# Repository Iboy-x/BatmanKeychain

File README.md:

# Batman Keychain

Wanted to save Gotham and proove your friends that you are Batman ? This Keychain is best!

## Schematic

## PCB

## 3D view

## Features
- LED on eyes that works when you press the button
- Motor that vibrates in pressing button 

## BOM
- 1 	Battery holder
- 2   LEDs 
- 2 	220 Resistor
- 1 	Push Button
- 1   Motor DC vibrator

Made by `@AbdulMoiz Adeel` on slack :D

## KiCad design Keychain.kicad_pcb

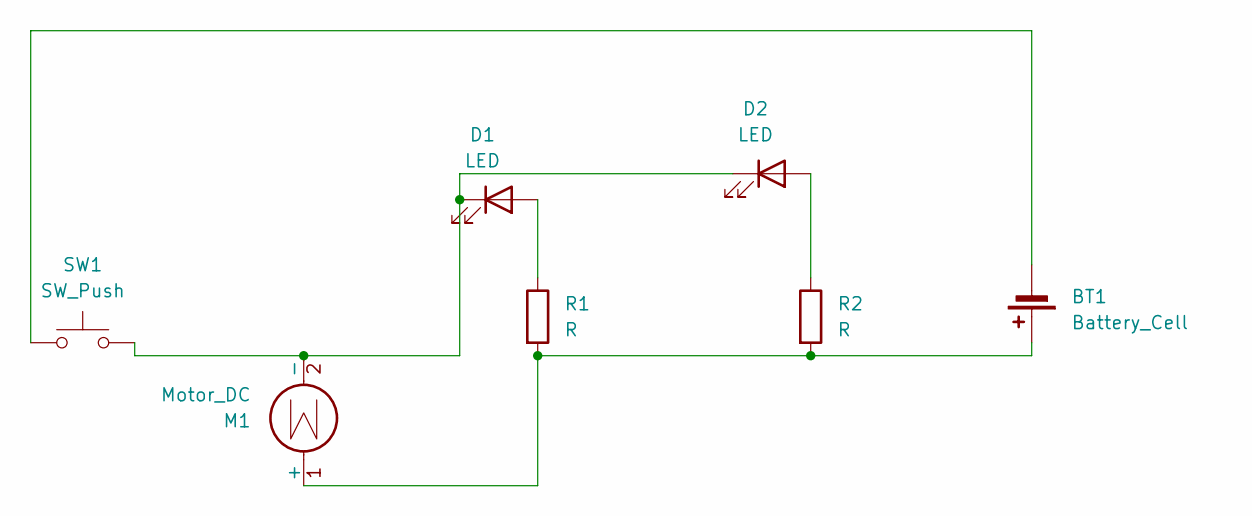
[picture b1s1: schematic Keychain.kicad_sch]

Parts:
BT1: Battery_Cell; BatteryHolder_Keystone_3034_1x20mm
D1, D2: LED; LED_D5.0mm
M1: Motor_DC; PinHeader_1x02_P2.54mm_Vertical
R1, R2: R; R_Axial_DIN0207_L6.3mm_D2.5mm_P7.62mm_Horizontal
SW1: SW_Push; SW_PUSH_6mm

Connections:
unnamed: BT1.1 (+), M1.1 (+), R1.2, R2.2
unnamed: BT1.2 (-), SW1.1
unnamed: D1.2 (A), R1.1
unnamed: D1.1 (K), D2.1 (K), M1.2 (-), SW1.2
unnamed: D2.2 (A), R2.1

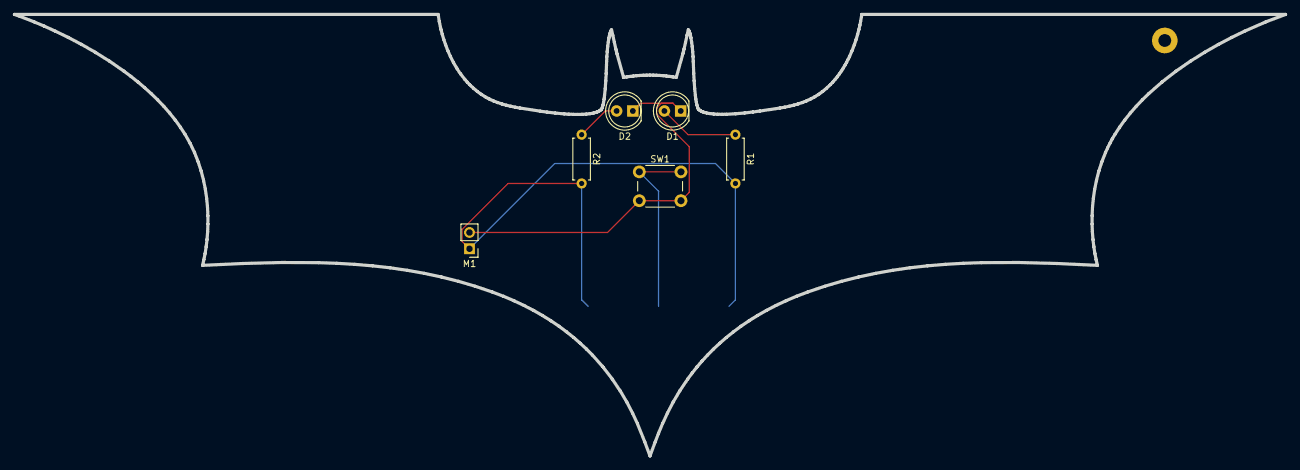
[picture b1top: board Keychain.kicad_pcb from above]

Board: 2 copper layers, 198.4 x 68.9 mm, 7 parts (1 on the bottom side), 5 nets.
